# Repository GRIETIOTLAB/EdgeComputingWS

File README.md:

# EdgeComputingWS
C code for the G-Edge board and Python code for ML using G-Edge datasets

The G-Edge board based on the ESP32 processor has the following sensors/actuators:
- DHT11 Temperature & Humidity sensor
- TCS3200 Color sensor
- MPU6050 Multi-axes accelerometer and gyro sensor
- Relay

The codes are in 3 categories:
- Basic sensor reading - C code to be run on the G-Edge board
- Generating datasets - C code to be run on the G-Edge board
- Google Colab notebooks for ML model generation using G-Edge datasets
- Inference code to be run on G-Edge with the trained model in place

The procedure for making the Arduino IDEraedy to program the ESP32 boards is as under:

https://circuitdigest.com/microcontroller-projects/programming-esp32-with-arduino-ide

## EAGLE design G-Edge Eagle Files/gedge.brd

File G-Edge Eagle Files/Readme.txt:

The folder contains the following Eagle files for the G_Edge board:
- Schematic file
- Board file

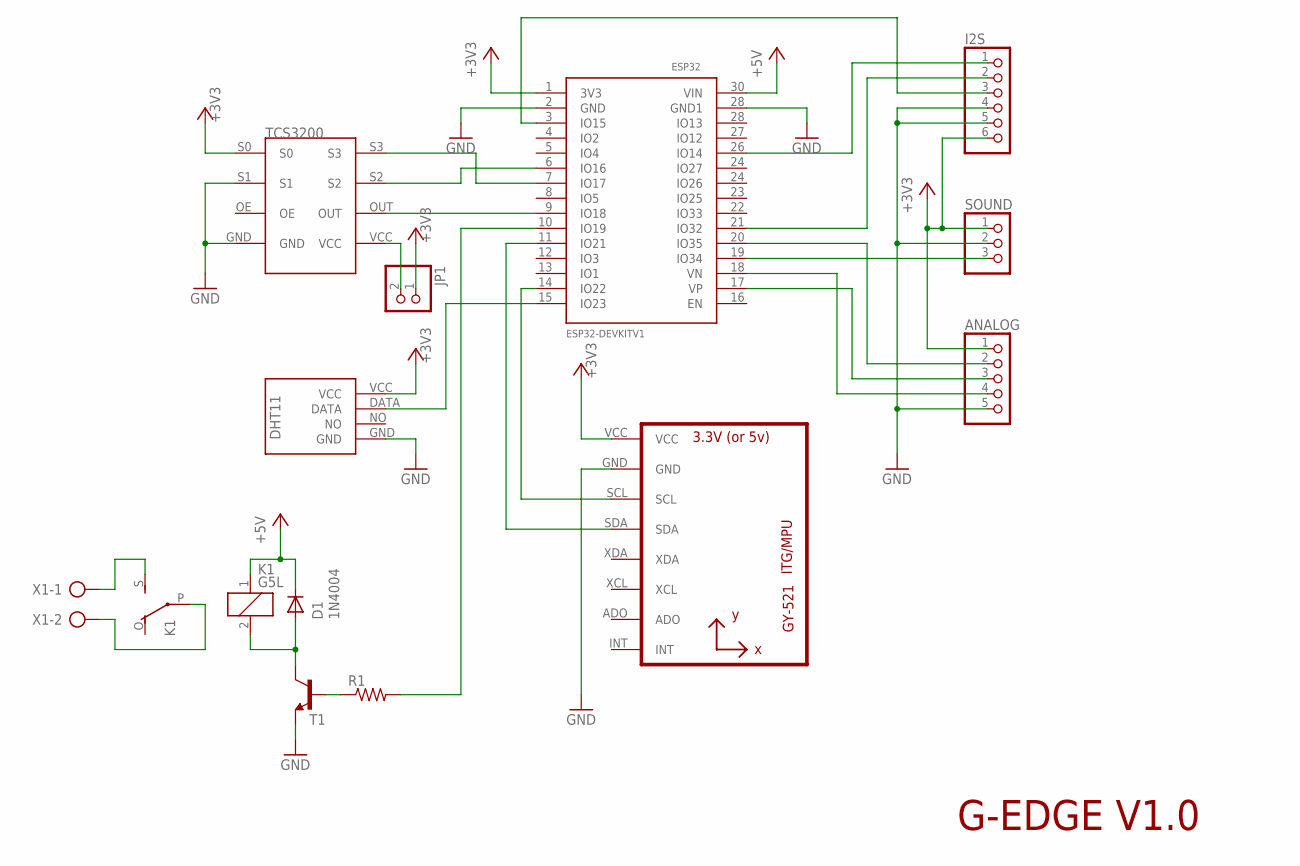
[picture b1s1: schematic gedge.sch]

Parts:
ANALOG: PINHD-1X5; 1X05
D1: 1N4004; DO41-10
ESP32: ESP32DEVKITV1; ESP32-DEVKITV1
I2S: PINHD-1X6; 1X06
JP1: PINHD-1X2; 1X02
K1: G5L; G5LE
R1: R-US_0204/7; 0204/7
SOUND: PINHD-1X3; 1X03
T1: BC107A-NPN-TO18-EBC; TO18
TCS3200: TCS3200
U1: GY-521MPU6050; GY-521
U$2: DHT11
X1: AK500/2

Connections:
+3V3: ANALOG.1, ESP32.1 (3V3), I2S.6, JP1.1, SOUND.1, TCS3200.S0, U1.VCC, U$2.VCC
+5V: D1.C, ESP32.30 (VIN), K1.1
GND: ANALOG.5, ESP32.2 (GND), ESP32.28 (IO13), I2S.4, I2S.5, SOUND.2, T1.1 (E), TCS3200.GND, TCS3200.S1, U1.GND, U$2.GND
unnamed: ESP32.6 (IO16), TCS3200.S2
unnamed: ESP32.7 (IO17), TCS3200.S3
unnamed: ESP32.19 (IO34), SOUND.3
unnamed: JP1.2, TCS3200.VCC
unnamed: ESP32.9 (IO18), TCS3200.OUT
unnamed: ESP32.15 (IO23), U$2.DATA
unnamed: D1.A, K1.2, T1.3 (C)
unnamed: K1.P, X1.2
unnamed: K1.S, X1.1
unnamed: R1.1, T1.2 (B)
unnamed: ESP32.10 (IO19), R1.2
unnamed: ESP32.14 (IO22), U1.SCL
unnamed: ESP32.11 (IO21), U1.SDA
unnamed: ANALOG.2, ESP32.20 (IO35)
unnamed: ANALOG.3, ESP32.17 (VP)
unnamed: ANALOG.4, ESP32.18 (VN)
unnamed: ESP32.3 (IO15), I2S.3
unnamed: ESP32.21 (IO32), I2S.2
unnamed: ESP32.26 (IO14), I2S.1

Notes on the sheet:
G-EDGE V1.0

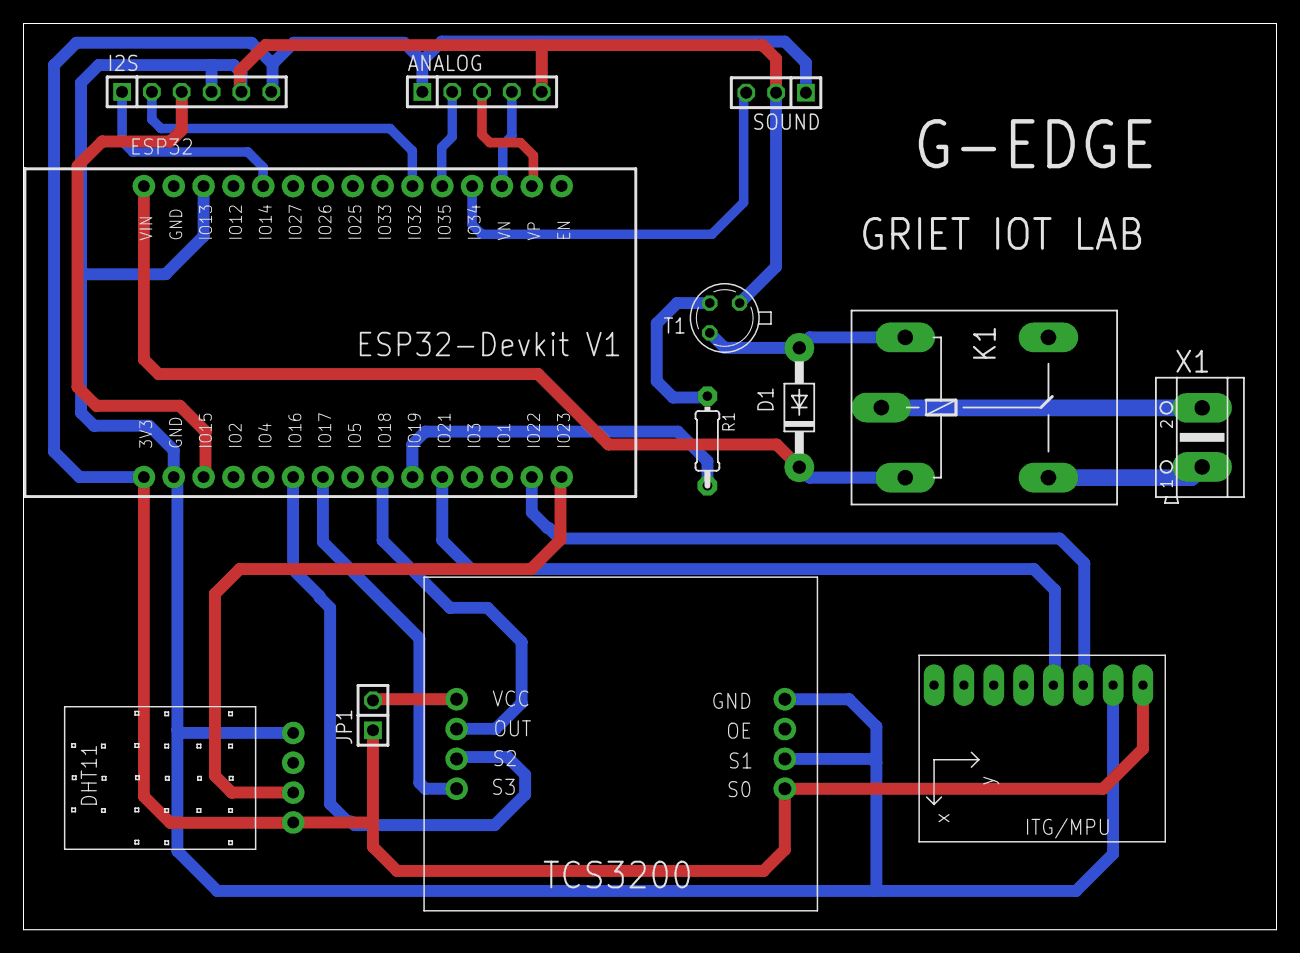
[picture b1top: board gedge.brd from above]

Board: 2 copper layers, 106.7 x 77.1 mm, 13 parts (0 on the bottom side), 22 nets.

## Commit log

2021-01-25 Created using Colaboratory
